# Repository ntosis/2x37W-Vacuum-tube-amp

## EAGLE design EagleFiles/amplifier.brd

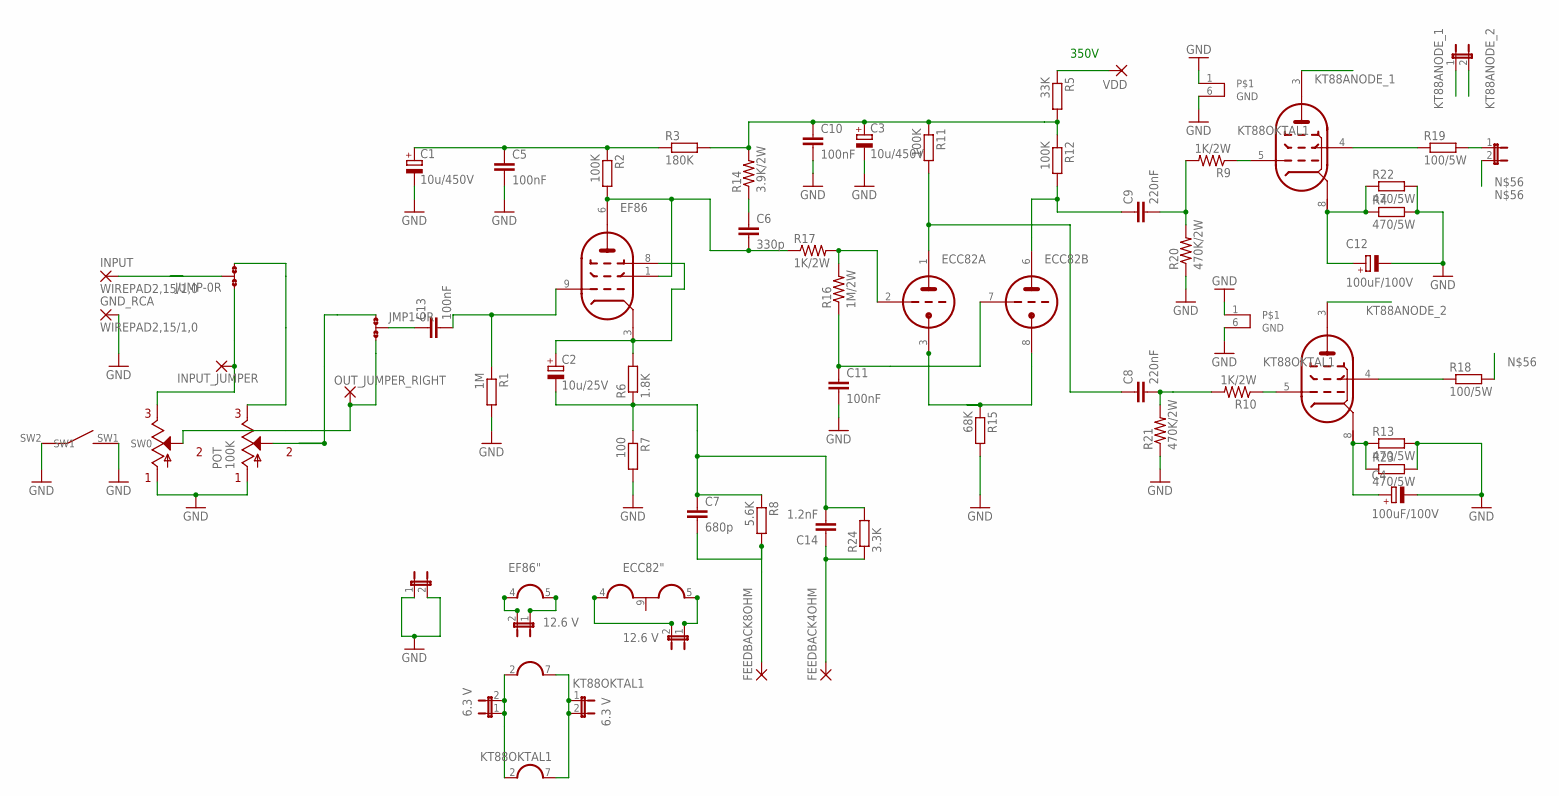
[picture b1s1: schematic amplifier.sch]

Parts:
6.3_KT88, 6.3_KTGND: 6.3 V; JP1
12.6V_ECC82, 12.6_EF86: 12.6 V; JP1
C1, C3: 10u/450V; E5-10,5
C2: 10u/25V; E3,5-10
C4, C12: 100uF/100V; E3,5-10
C5, C10, C11: 100nF; C7.5B3
C6: 330p; C5B5.5
C7: 680p; C5B5.5
C8, C9: 220nF; C7.5B3
C13: 100nF; C0805K
C14: 1.2nF; C5B5.5
ECC82: ECC82-P; NOVAL
EF86: EF86-P; NOVAL
FEEDBACK4OHM, FEEDBACK8OHM: 2,54/1,1
GND: JP1E; JP1
GND_RCA: WIREPAD2,15/1,0; 2,15/1,0
INPUT: WIREPAD2,15/1,0; 2,15/1,0
INPUT_JUMPER: 2,54/1,1
JMP1: 0R-JUMPA; A0R-JMP
JUMP: 0R-JUMPA; A0R-JMP
KT88_OUTPUT, KT88_TRAFO: JP1E; JP1
OUT_JUMPER_RIGHT: 2,54/1,1
POT: 100K; PTR902-2015K-A104
R1: 1M; R0805
R2, R11, R12: 100K; R0805
R3: 180K; R0805
R4, R13, R22, R23: 470/5W; 0617V
R5: 33K; R0805
R6: 1.8K; R0805
R7: 100; R0805
R8: 5.6K; R0805
R9, R10, R17: 1K/2W; R2512
R14: 3.9K/2W; R2512
R15: 68K; R0805
R16: 1M/2W; R2512
R18, R19: 100/5W; P0817V
R20, R21: 470K/2W; R2512
R24: 3.3K; R0805
U$2, U$3: KT88OKTAL1; OKTAL1
VDD: 2,54/1,1

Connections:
DIFFOUTPUT_N: C8.1, ECC82.1 (TA), R11.2
DIFFOUTPUT_P: C9.1, ECC82.6 (TA), R12.2
ECC82FILL+: 12.6V_ECC82.2, ECC82.4 (H1)
ECC82FILL-: 12.6V_ECC82.1, ECC82.5 (H3)
EF86FILL+: 12.6_EF86.2, EF86.4 (H1)
EF86FILL-: 12.6_EF86.1, EF86.5 (H2)
GND: C1.-, C3.-, C4.-, C5.2, C10.2, C11.2, C12.-, GND.1, GND.2, GND_RCA.1, POT.R1_1, POT.R2_1, POT.SW1 (SW0), POT.SW2 (SW1), R1.2, R4.2, R7.2, R13.2, R15.2, R20.1, R21.1, R22.2, R23.2, U$2.1, U$2.6 (GND), U$3.1, U$3.6 (GND)
KT88ANODE_1: KT88_OUTPUT.1, U$2.3 (ANODE)
KT88ANODE_2: KT88_OUTPUT.2, U$3.3 (ANODE)
KT88FILLAMENT+: 6.3_KT88.1, 6.3_KT88.2, U$2.2 (H1), U$3.2 (H1)
KT88FILLAMENT-: 6.3_KTGND.1, 6.3_KTGND.2, U$2.7 (H2), U$3.7 (H2)
KT88GRID_1: C9.2, R9.2, R20.2
KT88GRID_2: C8.2, R10.2, R21.2
KT88KATHODE_1: C12.+, R4.1, R22.1, U$2.8 (KATHODE)
KT88KATHODE_2: C4.+, R13.1, R23.1, U$3.8 (KATHODE)
unnamed: INPUT.1, JUMP.2
unnamed: C13.2, EF86.9 (PG), R1.1
unnamed: C2.+, EF86.3 (PK), EF86.8 (PBG), R6.2
unnamed: C6.2, EF86.1 (PSG), EF86.6 (PA), R2.2, R17.1
unnamed: C1.+, C5.1, R2.1, R3.1
unnamed: C3.+, C10.1, R3.2, R5.2, R11.1, R12.1, R14.2
unnamed: ECC82.2 (TG), R16.2, R17.2
unnamed: C6.1, R14.1
unnamed: C2.-, C7.1, C14.2, R6.1, R7.1, R8.1, R24.2
unnamed: C7.2, FEEDBACK8OHM.1, R8.2
unnamed: C11.1, ECC82.7 (TG), R16.1
unnamed: C14.1, FEEDBACK4OHM.1, R24.1
unnamed: R9.1, U$2.5 (INPUT)
unnamed: R10.1, U$3.5 (INPUT)
unnamed: R18.1, U$3.4 (OUTPUT)
unnamed: JMP1.1, POT.R1_2
unnamed: JUMP.3, POT.R1_3
unnamed: R19.1, U$2.4 (OUTPUT)
unnamed: ECC82.3 (TK), ECC82.8 (TK), R15.1
unnamed: R5.1, VDD.1
unnamed: JMP1.3, OUT_JUMPER_RIGHT.1, POT.R2_2
unnamed: KT88_TRAFO.1, R19.2
unnamed: INPUT_JUMPER.1, JUMP.1, POT.R2_3
unnamed: C13.1, JMP1.2
unnamed: KT88_TRAFO.2, R18.2

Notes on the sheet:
350V

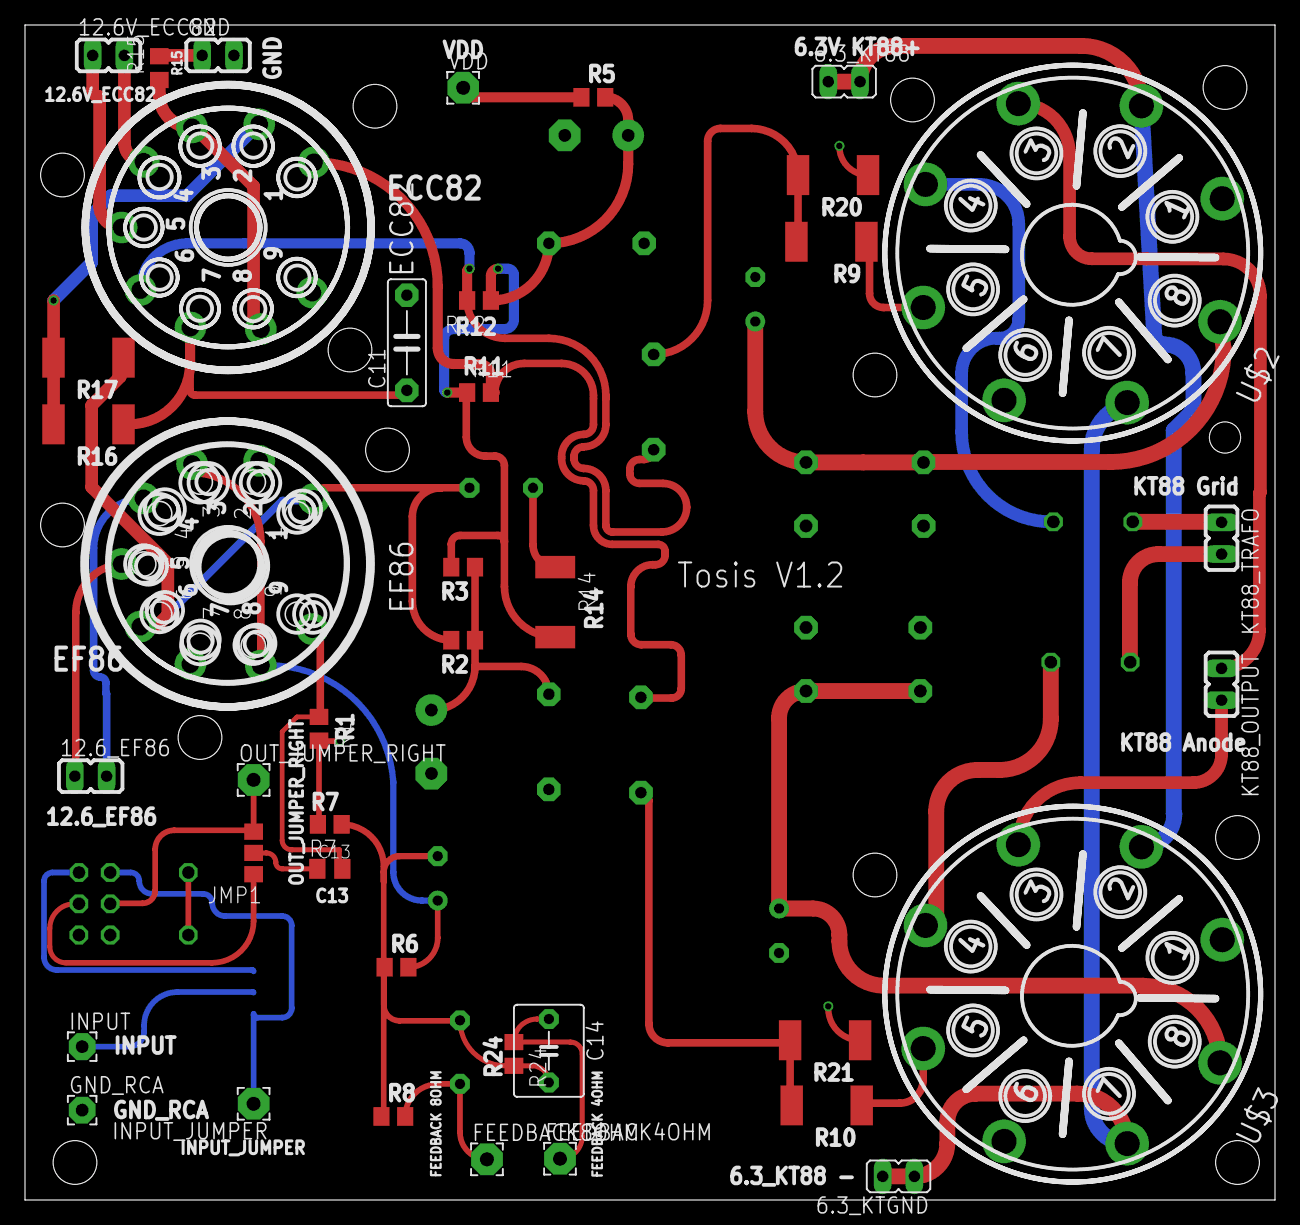
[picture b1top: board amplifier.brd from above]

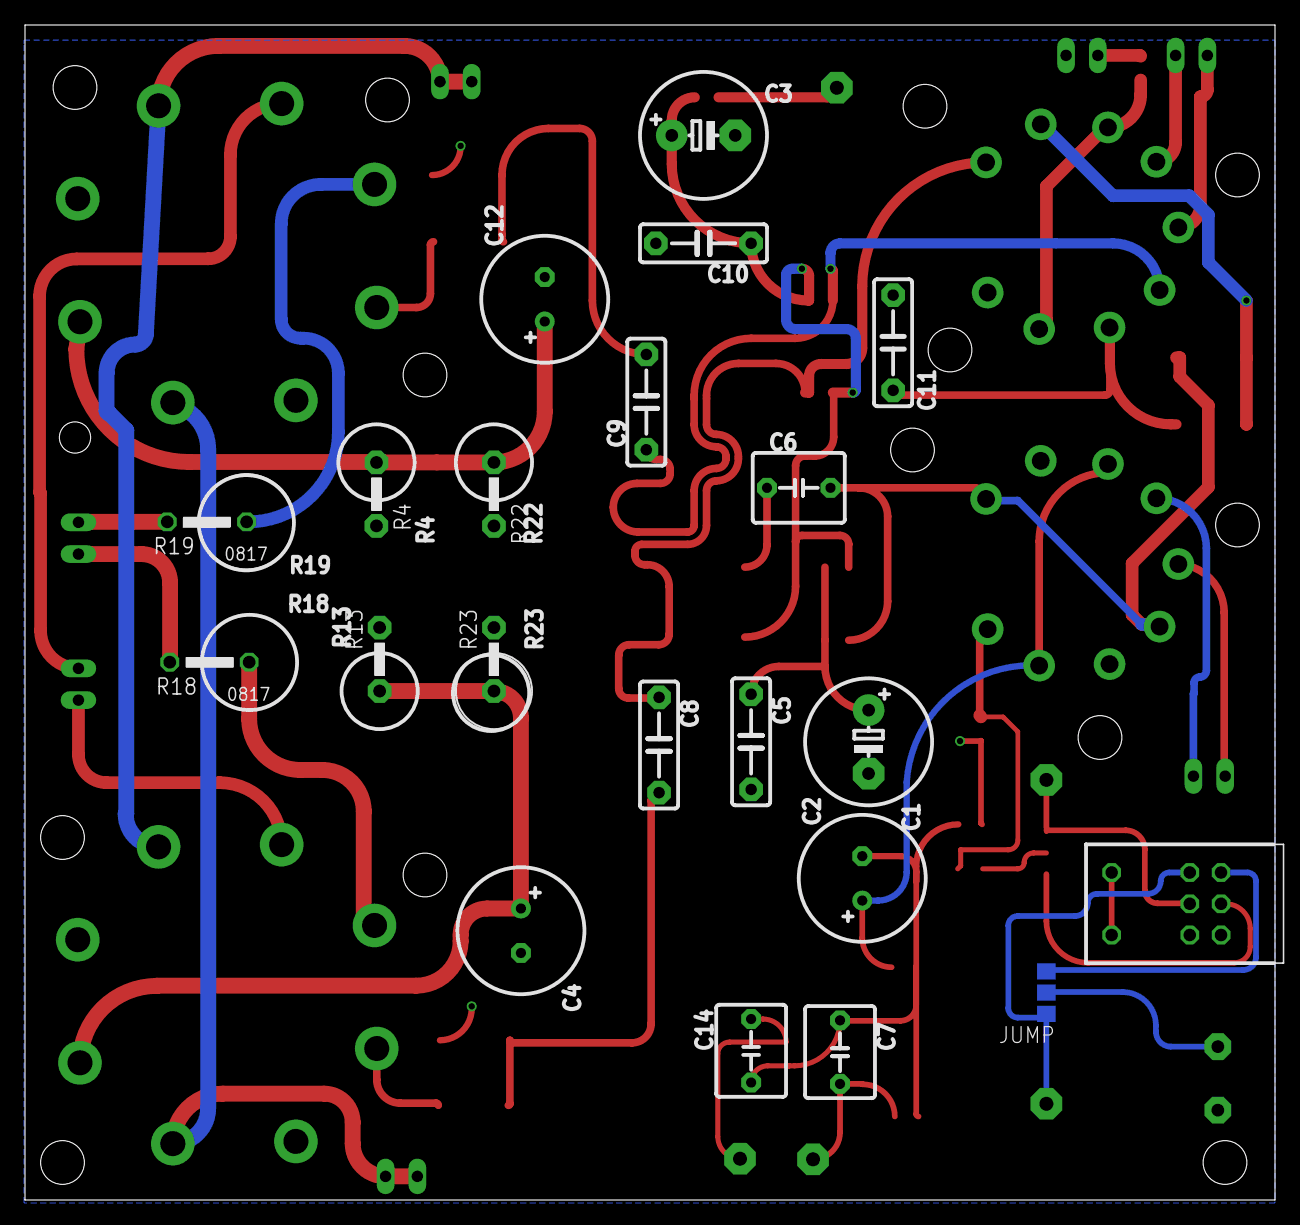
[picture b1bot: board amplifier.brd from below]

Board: 2 copper layers, 100.0 x 94.0 mm, 59 parts (19 on the bottom side), 40 nets.

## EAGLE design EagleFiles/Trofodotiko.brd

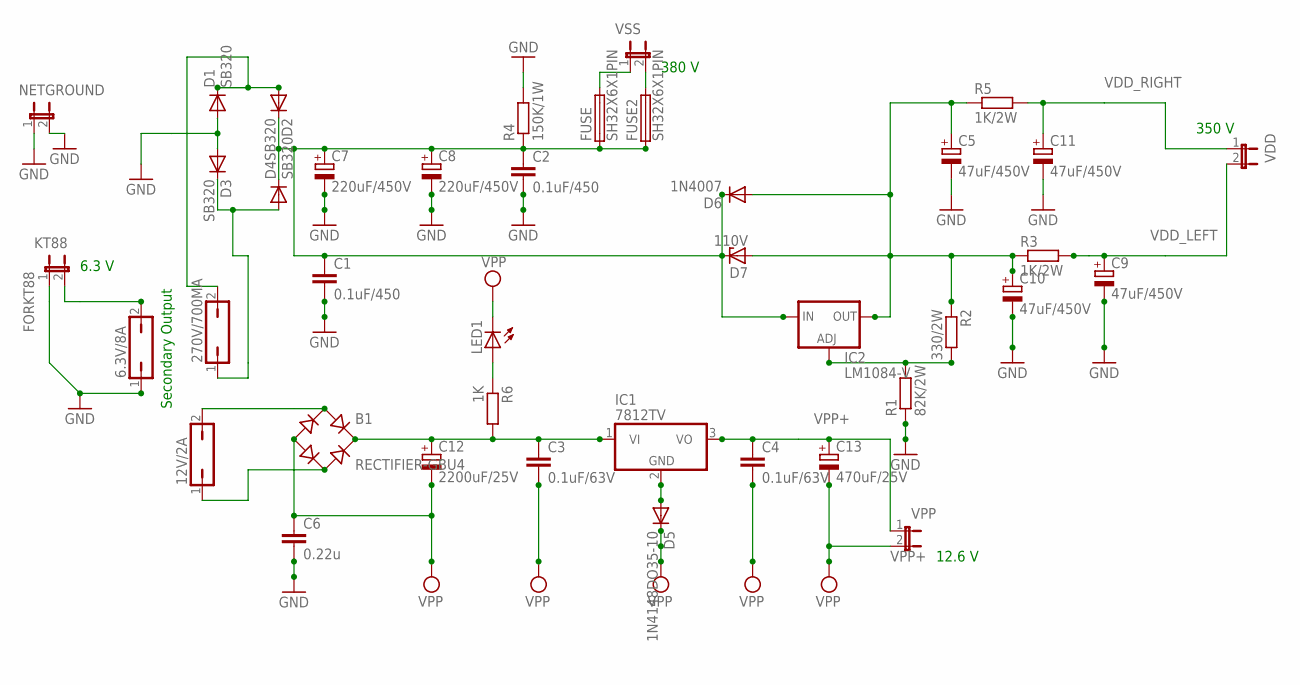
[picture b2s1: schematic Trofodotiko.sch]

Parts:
6.3V/8A, 12V/2A, 270V/700MA: JP1Q; JP1
B1: RECTIFIER-GBU4; GBU4
C1, C2: 0.1uF/450; C10B5
C3, C4: 0.1uF/63V; C5B2.5
C5, C9, C10, C11: 47uF/450V; E5-13
C6: 0.22u; C0805K
C7, C8: 220uF/450V; EB25D
C12: 2200uF/25V; E5-13
C13: 470uF/25V; E3,5-8
D1, D2, D3, D4: SB320; DO201-15
D5: 1N4148DO35-10; DO35-10
D6: 1N4007; DO15-12
D7: 110V; C1702-15
FUSE, FUSE2: SH32X6X1PIN; SH32
IC1: 7812TV; TO220V
IC2: LM1084-V; 317TS
KT88: JP1E; JP1
LED1: LEDSML0805; SML0805
NETGROUND: JP1E; JP1
R1: 82K/2W; P0817/22
R2: 330/2W; 0411/12
R3, R5: 1K/2W; 0411/12
R4: 150K/1W; 0411/15
R6: 1K; R0805
VDD: JP1E; JP1
VPP: JP1E; JP1
VSS: JP1E; JP1

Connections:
FORKT88: 6.3V/8A.2, KT88.2
GND: 6.3V/8A.1, C1.2, C2.2, C5.-, C6.2, C7.-, C8.-, C9.-, C10.-, C11.-, D1.A, D3.A, KT88.1, NETGROUND.1, NETGROUND.2, R1.1, R4.2
unnamed: 270V/700MA.2, D1.C, D2.A
unnamed: LED1.A, R6.1
unnamed: C1.1, C2.1, C7.+, C8.+, D2.C, D4.C, D6.C, D7.C, FUSE.1A (1), FUSE2.1A (1), IC2.3 (IN), R4.1
unnamed: 270V/700MA.1, D3.C, D4.A
unnamed: 12V/2A.2, B1.AC1
unnamed: 12V/2A.1, B1.AC2
unnamed: B1.+, C3.1, C12.+, IC1.1 (VI), R6.2
unnamed: C5.+, C10.+, D6.A, D7.A, IC2.2 (OUT), R2.1, R3.1, R5.1
unnamed: FUSE.2B (2), VSS.1
unnamed: FUSE2.2B (2), VSS.2
unnamed: IC2.1 (ADJ), R1.2, R2.2
unnamed: D5.A, IC1.2 (GND)
VDD_LEFT: C9.+, R3.2, VDD.2
VDD_RIGHT: C11.+, R5.2, VDD.1
VPP: B1.-, C3.2, C4.2, C6.1, C12.-, C13.-, D5.C, LED1.C, VPP.2
VPP+: C4.1, C13.+, IC1.3 (VO), VPP.1

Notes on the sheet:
12.6 V
6.3 V
380 V
350 V
Secondary Output

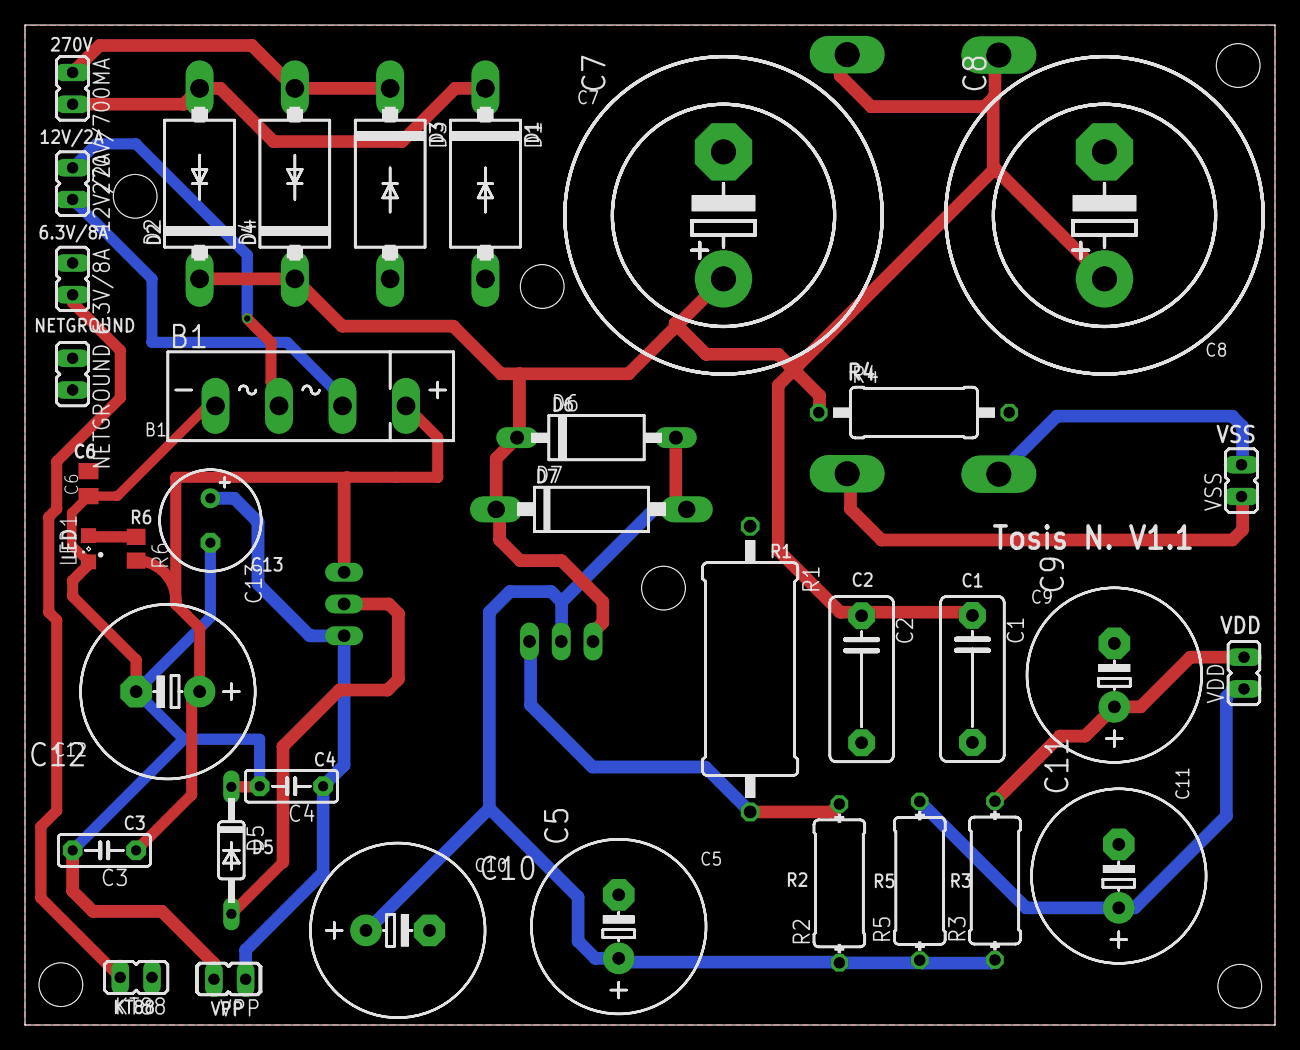
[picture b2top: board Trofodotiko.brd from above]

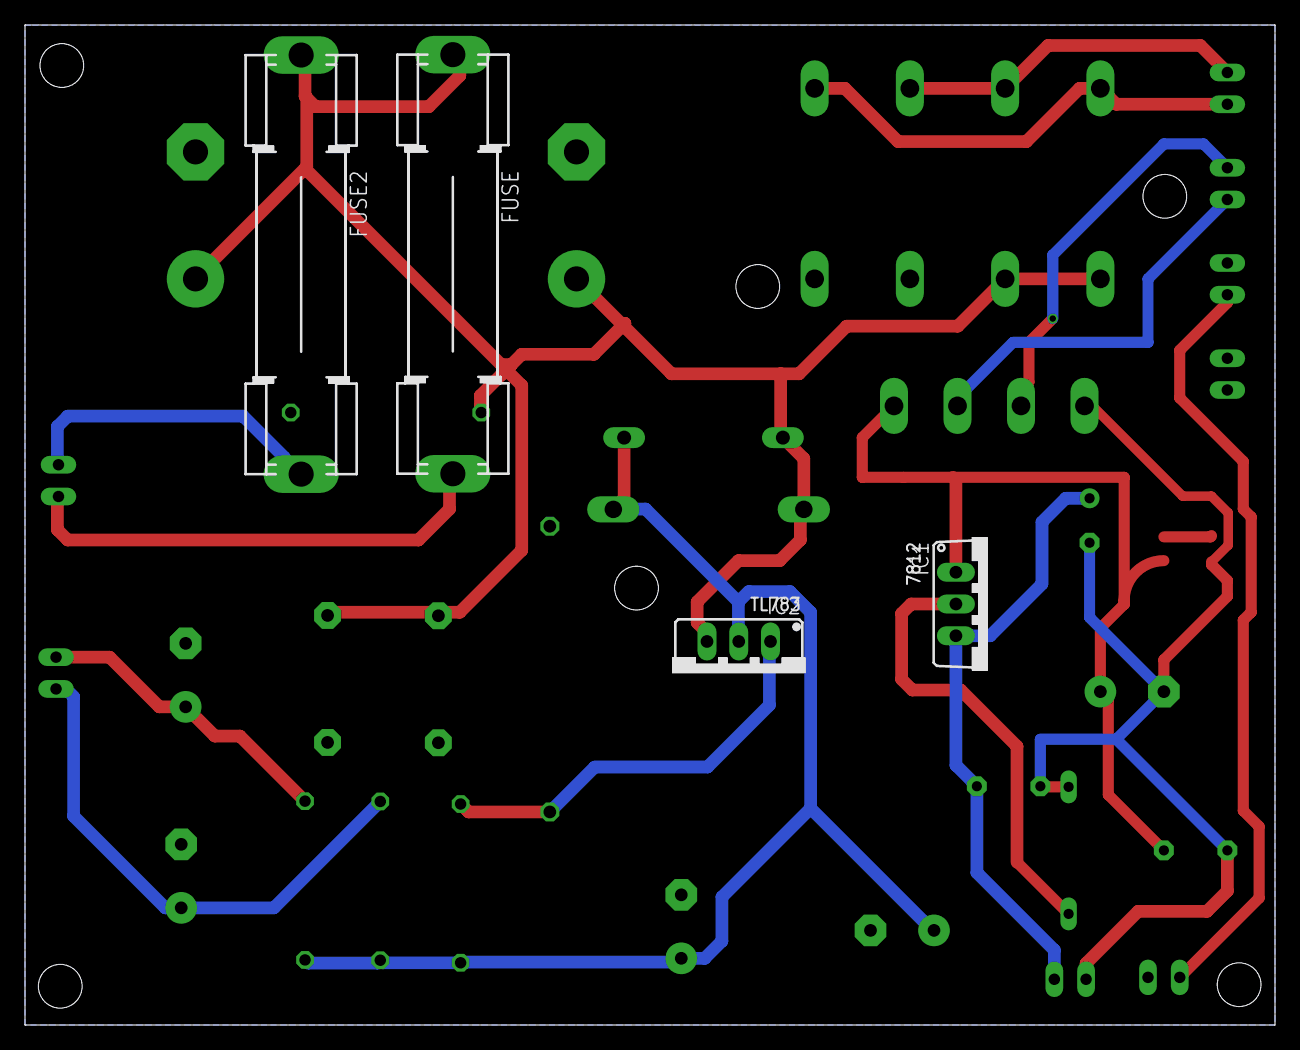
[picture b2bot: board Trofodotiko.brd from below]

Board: 2 copper layers, 100.0 x 80.0 mm, 40 parts (4 on the bottom side), 18 nets.

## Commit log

2018-12-16 Fix Feedback
2019-01-19 last not good design.
2019-01-27 back to old design, bigger dimensions and 2 feedbacks.
2019-01-27 grid resistor closer to tube pins.
2019-05-10 final version
